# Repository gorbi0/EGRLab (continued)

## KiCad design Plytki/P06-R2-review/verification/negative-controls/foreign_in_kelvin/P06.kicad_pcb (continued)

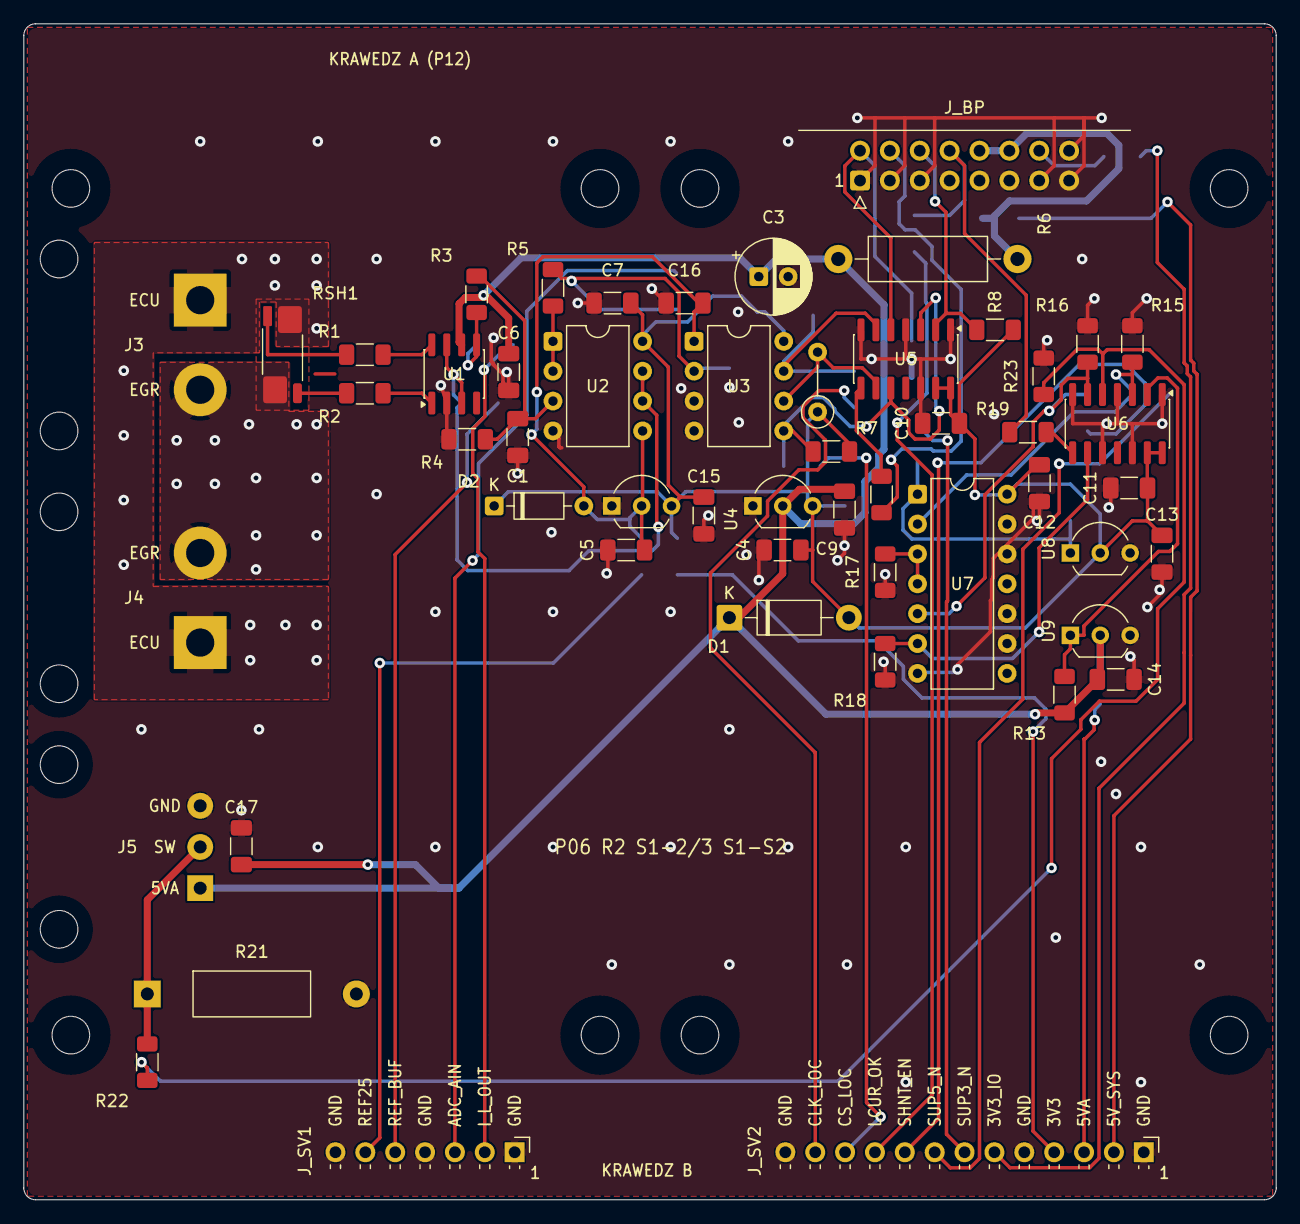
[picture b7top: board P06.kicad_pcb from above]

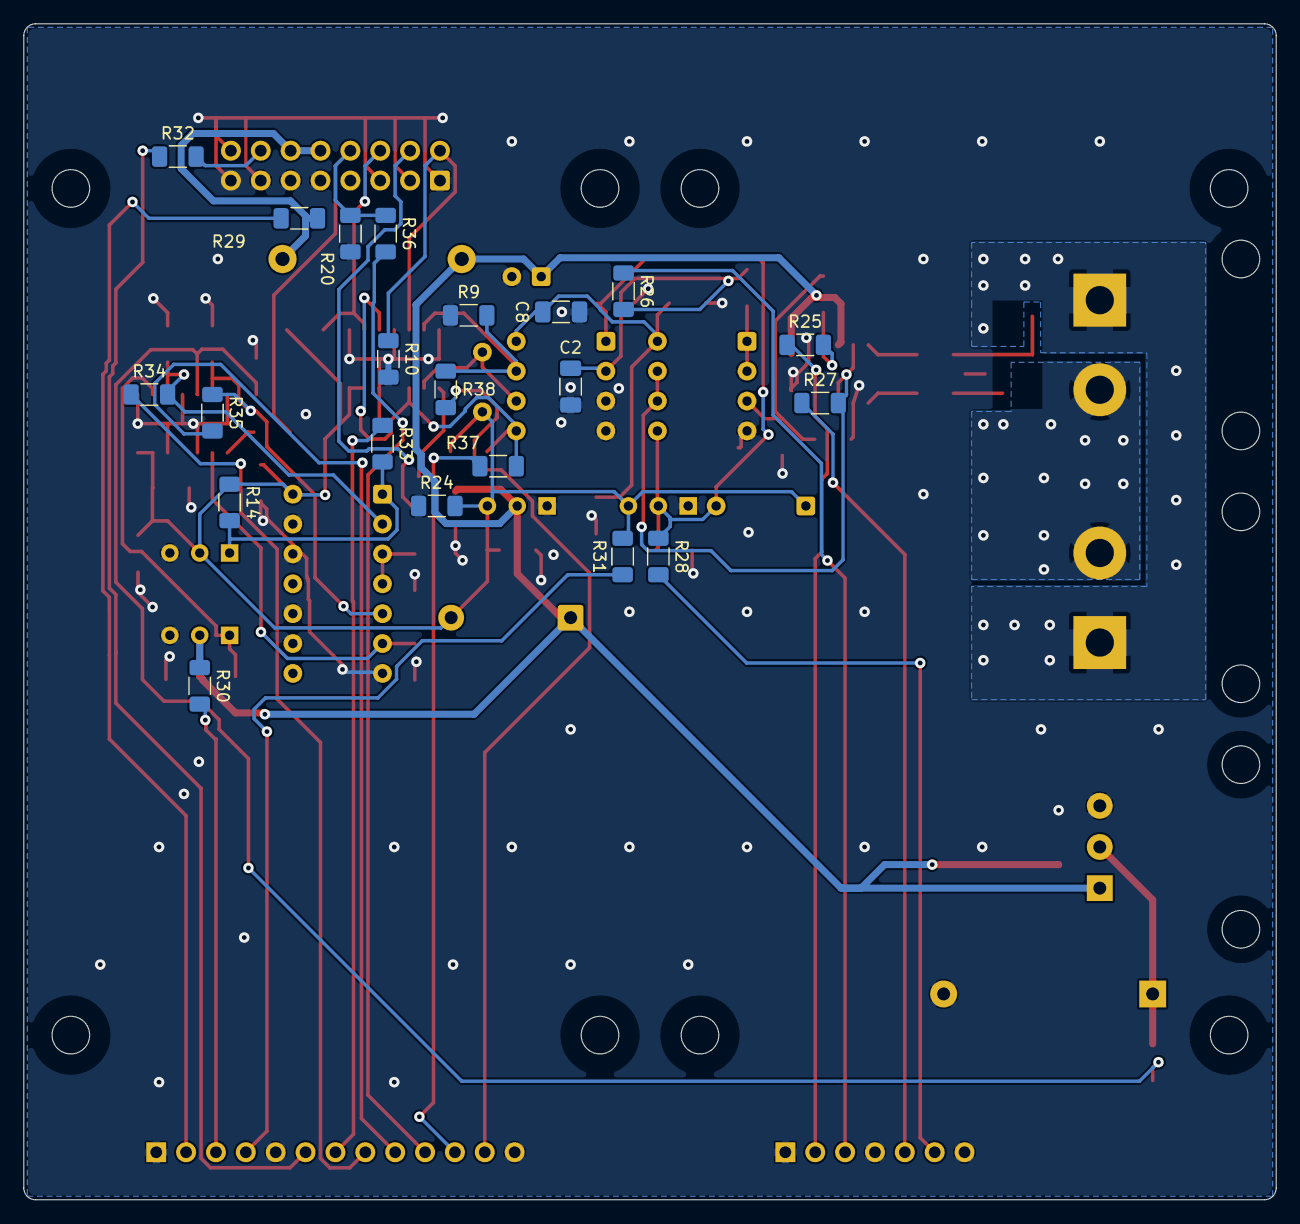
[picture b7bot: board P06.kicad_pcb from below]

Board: 2 copper layers, 106.5 x 100.0 mm, 82 parts (21 on the bottom side), 48 nets.

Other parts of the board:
C1: 470n; C_1206_3216Metric_Pad1.33x1.80mm_HandSolder
C5: 4.7u; C_1206_3216Metric_Pad1.33x1.80mm_HandSolder
C6: 100n; C_1206_3216Metric_Pad1.33x1.80mm_HandSolder
D2: BAT85; D_DO-35_SOD27_P7.62mm_Horizontal
H1, H2, H3, H4, H5, H6, H7, H8: M3 NPTH
R1, R2: 10R; R_1206_3216Metric_Pad1.30x1.75mm_HandSolder
R3, R4: 5.11K; R_1206_3216Metric_Pad1.30x1.75mm_HandSolder
U1: INA240A2; SOIC-8_3.9x4.9mm_P1.27mm
U10: MCP1525-I/TO; TO-92_Inline_Wide

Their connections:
3V3_P06: D2.1, U10.3; also elsewhere on the board
5VA_P06: C6.1, U1.6; also elsewhere on the board
/ANA/INA_MINUS: R2.2, U1.1
/ANA/INA_PLUS: R1.2, U1.8
/ANA/I_DIV: C1.1, R3.2, R4.1; also elsewhere on the board
GND: C1.2, C5.2, C6.2, R4.2, U1.2, U10.1; also elsewhere on the board
I_L_OUT: R3.1, U1.5; also elsewhere on the board
K_MINUS: R2.1; also elsewhere on the board
K_PLUS: R1.1; also elsewhere on the board
REF25: C5.1, D2.2, U10.2; also elsewhere on the board
REF_BUF: U1.3, U1.7; also elsewhere on the board

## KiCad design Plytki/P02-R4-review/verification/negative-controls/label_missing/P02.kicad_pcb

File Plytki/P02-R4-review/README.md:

# P02 R4 — zasilanie z pakietu Li-ion 4S (etap 2: PCB w formacie S1, klasa L)

**Nadruk 2.10.2026 (gałąź `p02-r4-nadruk`, przed zamówieniem):** wszystkie napisy ≥ 1,0 mm, linia ≥ 0,15 mm (minimum JLCPCB; ustalenie niezależnych recenzji P05 / P06), minimum w regułach DRC (`set_rules.py`). Miedź, otwory i rozmieszczenie bez zmian (wydanie odtworzone z zapisanego trasowania); paczka `P02-PCB-R4-zamowienie` zbudowana od nowa (DRC 0/0/0, CAM 20/20, próby CAM 8/8).

29.09.2026 schemat (sesja w chmurze, etap 1), 29–30.09.2026 PCB (lokalnie, etap 2). **Status: PCB i kontrole do recenzji. Pliki produkcyjne (Gerber, wiercenia), przymiarka 1:1 i zakupy nie są zrobione.** R4 zastępuje P01 PROTECT i część HOLD płytki P02 R3 zgodnie ze specyfikacją `Plytki/P02-R4-specyfikacja/` (D-01…D-07 przyjęte, R23 = 22 kΩ / 0,5 W). Zamknięte pakiety P01 R3 i P02 R3 nie zostały zmienione, generatory skopiowano stamtąd.

## Co jest na płytce

- **WEJ** (plik `P02.kicad_sch`): J1 z pakietu, Q9 (Q_REV) i Q1 (Q_SW) — dwa SUP53P06 połączone przeciwsobnie źródłami w SW_COM; tor bramki Q1 z szybkim wyłączaniem Q2 (Q_OFF) i Q3–Q5 przeniesiony 1:1 z P01 R3 (poza R23). Dalej VSW (5KP18A, 47 µF), VMOTOR przez F1 5 A MINI, D1 (suma VSW i C_H → VLOG), podtrzymanie R40 22 Ω bezpiecznikowy → D2 → C12 2200 µF.
- **STER**: AUX5 z LM2936 zasilanego z SW_COM lub VLOG (D11/D12), REF TL431, UVLO na U2B z przełącznikiem PWR (J14) w górnej gałęzi dzielnika, OK z resetem U4, ENABLE przez D7/D8/Q6, PFAIL_N z U2A, SAFE_N/PG do P04 (Q7/Q8, R34, J13) i LED PWR.
- **LV**: TSR 2-2450 i TSR 2-2433 za F2/F3 1 A MINI, J3–J10 bez zmian.
- **MON**: PSU_OK jak R3 (U7, U8, U9 na adapterze, U10A; bramki HOLD_READY usunięte), J12 z PFAIL_N na pinie 3, VBAT auta J15 → R38 10 kΩ → D13 P6KE24CA → J11 Mini-Fit 2p.

Oznaczenia: tor sterowania ma numery z P01 R3 (Q1–Q8, R1–R4, R13–R34, C1–C11, D3/D4/D7–D9, U1–U4), elementy z P02 R3 dostały nowe numery. Pole `source_ref` w `docs/parts.json` podaje pochodzenie każdej części (`P01R3:…`, `P02R3:…`, `R4:NEW`): 54 z P01 R3, 34 z P02 R3, 43 nowe (w tym 17 punktów pomiarowych).

## Wyniki (szczegóły: `verification/QA.md`, `docs/OBLICZENIA-R4.md`)

| Kontrola | Wynik |
|---|---|
| ERC (4 arkusze) | 0 naruszeń |
| Netlista pin po pinie względem `parts.py` | 131 części, 317/317 pinów, 61 sieci |
| Kontrole elektryczne | 35/35 PASS |
| Próby ujemne | 19/19 (18 mutacji wykrytych + próba zerowa czysta) |
| UVLO nominalnie / obwiednia | 13,50 / 12,55 V; załączenie 12,90–14,08 V, wyłączenie 11,98–13,11 V, histereza ≥ 0,84 V |
| Wyłączenie Q1 (R23 22 kΩ) | 44–71 µs nominalnie, do 239 µs w narożniku (model skalibrowany na ngspice P01 R3: −6…−9 %) |
| Narastanie VSW / prąd przy 220 µF | 11,5 V/ms / 2,53 A nominalnie (5,6–14,7 V/ms, do 3,24 A w narożnikach) |
| Podtrzymanie po PFAIL_N przy 6 W | 16,8 ms nominalnie, 11,1 ms w najgorszym narożniku |

Niezgodności ze specyfikacją (do decyzji, opisane w `docs/OBLICZENIA-R4.md`): Z-02 (rozrzut większy niż ± 0,34 V), Z-08 (najgorszy narożnik 11,1 / 22,3 ms zamiast 14 / 28 ms), Z-01 (25 V wbrew 5KP18A). Odstępstwo projektowe: PFAIL_N z U2A buforującej OK zamiast porównania UV_CMP (D-06 dosłownie).

## Uruchomienie

W chmurze: `scripts/egrlab-docker python3 src/run_schematic.py` (ok. 20 s). Lokalnie: Python KiCada 10.0.6, `KICAD_CLI` i `PDFTOPPM` wskazują narzędzia. Kroki: budowa schematu → ERC → netlista → `verify_schematic.py` → `check_electrical.py --negative` → PDF i podglądy PNG → `verification/manifest.json`.

PCB (lokalnie, ok. 25 min): Python KiCada 10.0.6 `src/run_release.py` — schemat, płytka odtworzona z `routing/P02.ses` i `routing/completion-routes.json`, nadruk, `verify_pcb.py`, próby ujemne, widoki, PDF, QA i manifest. Zmienne: `EGRLAB_PDF_PYTHON` (reportlab), `EGRLAB_NODE` i `EGRLAB_SHARP` (rasteryzacja), `PDFTOPPM`; `--new-route` uruchamia Freerouting od nowa (`EGRLAB_FREEROUTING`). Trasowania nie robić w chmurze (`docs/CHMURA.md`, zasada 6).

## Zawartość

| Ścieżka | Zawartość |
|---|---|
| `eda/` | Projekt KiCad 10 (4 arkusze A3), lokalne biblioteki symboli i footprintów |
| `output/pdf/P02-R4-schemat.pdf`, `output/previews/` | Schemat i podglądy stron |
| `docs/parts.json`, `docs/BOM.csv` | Części, piny, sieci, MPN, pochodzenie |
| `docs/OBLICZENIA-R4.md` | UVLO, PFAIL_N, wyłączanie z R23, narastanie VSW, podtrzymanie, straty |
| `verification/` | ERC, netlista, kontrola pin po pinie, kontrole elektryczne, próby ujemne, logi, manifest SHA-256 |
| `src/` | Generatory (`cadlib.py`, `verify_schematic.py` z P02 R3), `parts.py`, `build_schematic.py`, `check_electrical.py`, `run_schematic.py` |

Footprinty TO-220, MFR-50, PR02, B32529, MKS2, P600 i wiązki PG pochodzą z bibliotek P01 R3 / P02 R3 (bez zmian), pozostałe z KiCad 10.0.6 albo z generatora w `parts.py`. W etapie 2 (PCB) trzeba potwierdzić: obrys C12 (16 × 25 mm, P7,5), oprawki MINI Keystone 3568, Mini-Fit 2p.

## Etap 2 — PCB (format S1, klasa L; lokalnie 29–30.09.2026)

**Płytka:** 160 × 100 mm, klasa L — cały poziom 1 stosu (sloty S1–S3; format S1-3: w klasie 2/3 trasowanie się nie domykało, decyzja użytkownika „opcja 1”). Dwie warstwy 35 µm, FR4 1,6 mm. J_BP (IDC 2×10 kątowe) na krawędzi A w slocie S3, listwy serwisowe J_SV1 (S1) i J_SV2 (S3) na krawędzi B, złącza pakietu i silnika przy ścianie wejść (x = 160).

**Rozmieszczenie** (`src/placement.py`):
- blok mocy z pilota 2/3 przesunięty o 53,5 mm do ściany wejść (wylewki, pasy 5 A i korytarz tym samym przesunięciem w `route_critical.py`); rdzeń mocy (Q9, Q1, Q2, sterowanie bramki, F1, D3) bez zmian — decyzja użytkownika 30.09, jego miedź jest narysowana wokół położeń części;
- blok sterowania rozsunięty w osi x od strony panelu dwa razy: ×1,35, potem na wskazanie użytkownika (wolne pole między blokami na wydruku 1:1) górna połowa ×1,25, dolna ×1,12; układy jadą sztywno ze swoimi kondensatorami odsprzęgającymi i rezystorami serwisowymi;
- grupa podtrzymania (C12, D1, D2, R40, R41, R67, C20, R68) 8 mm w lewo razem ze swoimi wylewkami VLOG/HOLD_C i przedłużeniami VSW; grupa ENABLE (Q6, D7, D8, R14–R16, R55) 4 mm w lewo;
- R5 (1 kΩ, początek dzielnika UVLO) obok D11 (SW_COM): PWR_A (R5 → J14 → włącznik na panelu) krótka, rezystor nadal przy źródle;
- zajętość obrysami w pasach 20 mm po rozsunięciu: 42 / 43 / 41 / 40 / 41 / 23 / 76 / 68 % (wcześniej 49 / 60 / 36 / 24 / 29 / 34 / 76 / 68 %).

**Trasowanie:** Freerouting 2.1.0, 30 przejść; domknęła się 1. próba (`routing/P02.ses`, `routing/attempts.json`). Planer dokańczania dołożył 7 tras w 7 sieciach (`routing/completion-routes.json`). Płytkę odtwarza `src/run_layout.py --reuse-ses` (bez routera).

**Poprawki łańcucha względem pilota** (w kodzie opisane datami 29–30.09):
- planer dokańczania kończy ścieżkę tylko na warstwie pola (wcześniej ścieżka B.Cu kończyła się na polu SMD F.Cu bez przelotki);
- zszywanie GND na całej długości płytki (pilot kończył siatkę na x = 104,5) i wiązanie klastrów GND bez połączenia z J1.2; kontrola obecności obu stref GND;
- porządki: przelotki na polach THT tej samej sieci, przelotki z miedzią na jednej warstwie; łańcuch uznawany za nadmiarowy tylko wtedy, gdy oba końce leżą na tej samej grupie zablokowanej miedzi;
- wylewki BAT_IN i VSW pod końcami blaszek Q9 i Q1 (wcześniej wchodził tam pasek GND);
- nadruk: etykiety listew przed oznaczeniami, oznaczenia poza nadrukiem części, litery „K” diod przesuwane z linii nadruku;
- kontrole: obrys bez grubości linii, tor 5 A liczony jako miedź sieci na przekroju, niezgodności z biblioteką tylko dla części z przyciętym nadrukiem; próby ujemne i PDF we współrzędnych klasy L.

**Wyniki** (`verification/QA-PCB.md`, `verification/pcb-checks.json`):

| Kontrola | Wynik |
|---|---|
| DRC (świeży, wszystkie poziomy) | 0 niepołączonych, 0 niezgodności ze schematem, 0 innych naruszeń; 14 × `lib_footprint_mismatch` u części, którym `silkscreen.py` przyciął nadruk lub przesunął tekst (lista w `routing/silkscreen.json`) |
| Kontrole PCB | 23/23 |
| Próby ujemne | 12/12 (w tym próba zerowa) |
| Tor 5 A — najwęższy przekrój miedzi (wymóg 4,0 mm, IPC-2152, 35 µm, ΔT ≤ 20 K) | BAT_IN 6,0; SW_COM 6,1; VSW 5,1; VMOTOR 5,7; powrót GND na B.Cu 4,1 mm |
| Pola z pełnym połączeniem ze strefą | C8.2, D3.2, LED1.1, U10.4, U2.4 (odciążenie „zagłodzone” przez sąsiednie ścieżki); złącza zachowują odciążenia |
| Wysokości | ≤ 21,5 mm; C27/C28 od spodu 0,88 mm (karta KEMET C1206C104K5RACTU, DigiKey 411248) |

**Do recenzji / otwarte:**
- przymiarka 1:1 (wydruk z `output/pdf/P02-R4-PCB.pdf`);
- 9 oznaczeń ukrytych z braku miejsca (R23, R22, Q2, Q9, F3, F1, F2, U6, U5); nie wstawione znaczniki „1” przy złączach (piny 1 oznacza nadruk footprintów);
- pola z pełnym połączeniem ze strefą GND lutować mocniejszą lutownicą — szczególnie D3.2 (wyprowadzenie transila P600);
- najwęższy przekrój toru 5 A: 4,1 mm;
- awaria jednego przebiegu wydania 30.09 (strefy GND zniknęły po imporcie SES, 204 niepołączenia) nie dała się odtworzyć; `stitch.py` zatrzymuje się teraz, gdy stref GND brakuje.

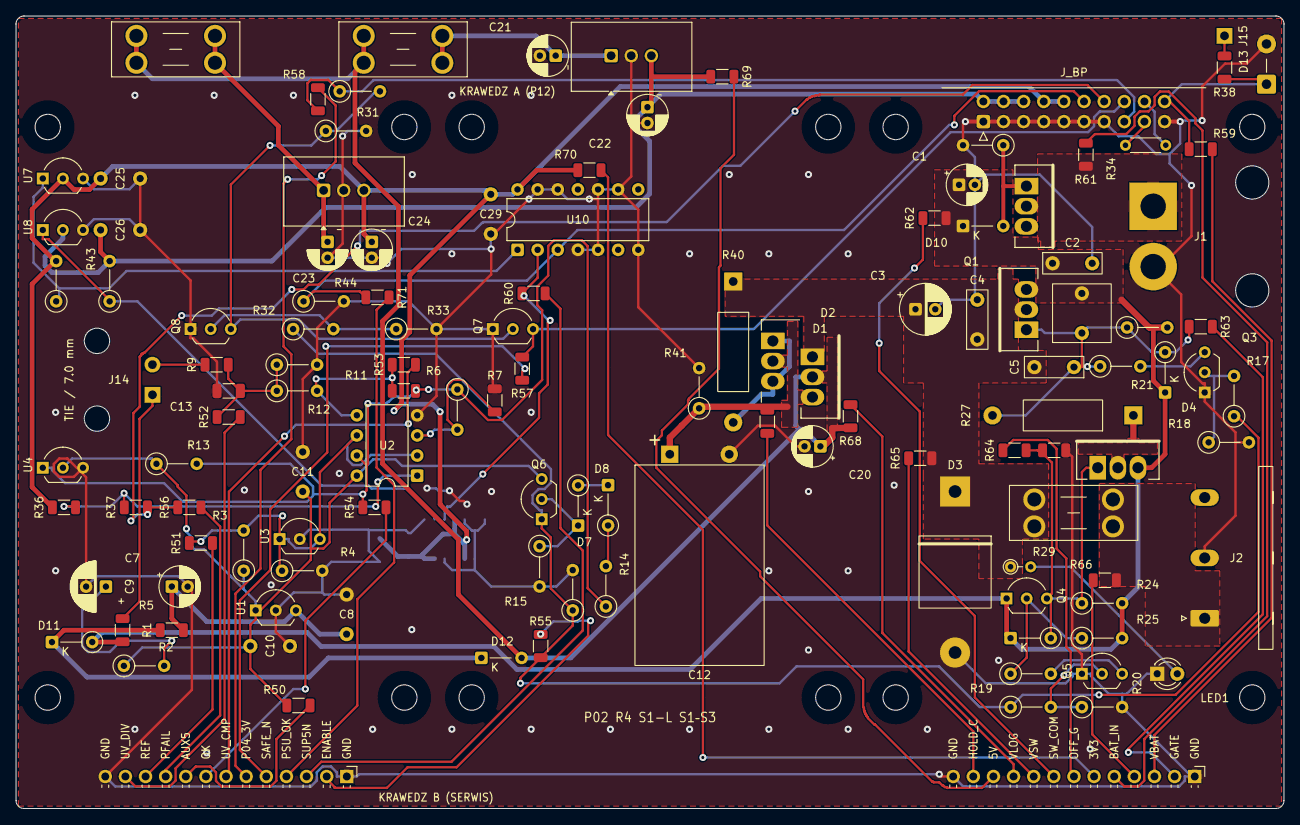
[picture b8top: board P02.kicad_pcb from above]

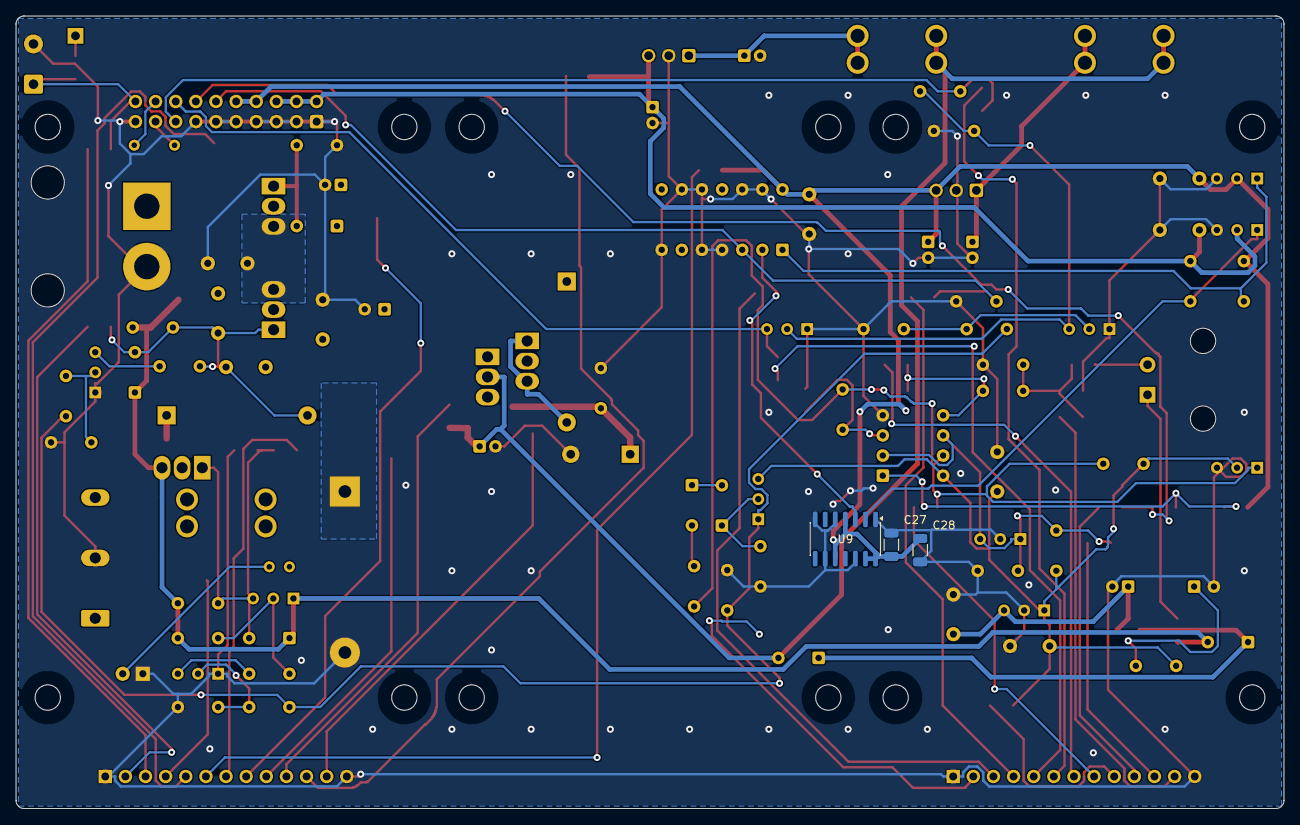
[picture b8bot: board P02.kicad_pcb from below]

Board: 2 copper layers, 160.0 x 100.0 mm, 139 parts (3 on the bottom side), 73 nets.

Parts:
C1, C21, C23: 10u; CP_Radial_D5.0mm_P2.00mm
C2, C4: 100nF; C_TDK_B32529_L7.3_W2.5_P5
C3, C9: 47u; CP_Radial_D6.3mm_P2.50mm
C5: 10nF; C_TDK_B32529_L7.3_W2.5_P5
C6: 1uF; C_WIMA_MKS2_1u100V_L7.2_W7.2_P5
C7, C20, C22, C24: 22u; CP_Radial_D5.0mm_P2.00mm
C8, C10, C11, C25, C26, C29: 100nF; C_Vishay_K15_H5_P5
C12: 2200u; CP_Radial_D16.0mm_L25mm_P7.50mm_Lying
C13: 10nF; C_1206_3216Metric
C27, C28: 100nF; C_1206_3216Metric
D1, D2: STPS20100CT; TO220_3_P2.54_Drill1.4
D3: 5KP24A; TVS_P600_P20.32
D4, D9, D10: BZX55C15; D_DO-35_SOD27_P5.08mm_Vertical_CathodeUp
D7, D8, D11, D12: 1N4148; D_DO-35_SOD27_P5.08mm_Vertical_CathodeUp
D13: P6KE24CA; D_DO-15_P5.08mm_Vertical_CathodeUp
F1: 5A; Fuseholder_Blade_Mini_Keystone_3568
F2, F3: 1A; Fuseholder_Blade_Mini_Keystone_3568
H1, H2, H3, H4, H5, H6, H7, H8, H9, H10, H11, H12: M3 NPTH
J1: BAT; Pigtail_PWR_2x2.5mm2
J2: VMOTOR; PhoenixContact_GMSTBA_2,5_3-G-7,62_1x03_P7.62mm_Horizontal
J14: PWR; Pigtail_PWR_SW_2xAWG22_T7
J15: VBAT_IN; Pigtail_VBAT_1xAWG22
J_BP: J_BP; IDC-Header_2x10_P2.54mm_Horizontal
J_SV1: J_SV1; PinHeader_1x13_P2.54mm_Horizontal
J_SV2: J_SV2; PinHeader_1x13_P2.54mm_Horizontal
LED1: GREEN 3mm; LED_D3.0mm
Q1, Q2, Q9: SUP53P06-20; TO220_3_P2.54_Drill1.4
Q3, Q5, Q6, Q7, Q8: 2N5551G; TO-92_Inline_Wide
Q4: 2N5401YBU; TO-92_Inline_Wide
R1: 47R; R_1206_3216Metric
R2: 1R; R_Axial_DIN0207_L6.3mm_D2.5mm_P5.08mm_Vertical
R3: 820R; R_Axial_DIN0207_L6.3mm_D2.5mm_P5.08mm_Vertical
R4, R10, R12, R16, R26, R30, R32, R41, R42, R43, R44: 10K; R_Axial_DIN0207_L6.3mm_D2.5mm_P5.08mm_Vertical
R5, R37, R50, R54, R55, R56, R57, R58, R60, R69, R70, R71: 1K; R_1206_3216Metric
R6, R15, R21, R24, R31, R35: 100K; R_Axial_DIN0207_L6.3mm_D2.5mm_P5.08mm_Vertical
R7: 150K; R_1206_3216Metric
R9: 41K2; R_1206_3216Metric
R11: 464K; R_1206_3216Metric
R13: 2K2; R_Axial_DIN0207_L6.3mm_D2.5mm_P5.08mm_Vertical
R14, R17, R19: 4K7; R_Axial_DIN0207_L6.3mm_D2.5mm_P5.08mm_Vertical
R18, R20, R25, R33: 47K; R_Axial_DIN0207_L6.3mm_D2.5mm_P5.08mm_Vertical
R22: 470K; R_Axial_DIN0207_L6.3mm_D2.5mm_P5.08mm_Vertical
R23: 22K; R_1206_3216Metric
R27: 10R; R_PR02_P17.78
R29: 6K8; R_Axial_DIN0204_L3.6mm_D1.6mm_P2.54mm_Vertical
R34: 0R; R_Axial_DIN0204_L3.6mm_D1.6mm_P5.08mm_Horizontal
R36, R38, R51, R52, R53, R59, R63, R64: 10K; R_1206_3216Metric
R40: 22R; R_PR02_P17.78
R61, R62, R65, R66, R67, R68: 4K7; R_1206_3216Metric
U1: LM2936Z-5.0; TO-92_Inline_Wide
U2: LM2903P; DIP-8_W7.62mm
U3: TL431BILP; TO-92_Inline_Wide
U4, U8: MCP120-450DI/TO; TO-92_Inline_Wide
U5: TSR 2-2450; Converter_DCDC_TRACO_TSR2-xxxx_THT
U6: TSR 2-2433; Converter_DCDC_TRACO_TSR2-xxxx_THT
U7: MCP120-300DI/TO; TO-92_Inline_Wide
U9: 74LVC125A; SOIC-14_3.9x8.7mm_P1.27mm
U10: SN74HC08N; DIP-14_W7.62mm

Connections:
3V3_IO: C24.1, C25.1, C27.1, C28.1, C29.1, J_BP.8, J_BP.10, R36.1, R42.2, R70.1, U6.3, U7.2, U9.4, U9.10, U9.13, U9.14, U10.14
5V_SYS: C22.1, C26.1, J_BP.2, J_BP.4, J_BP.6, R43.2, R69.1, U5.3, U8.2
/LV/P02_VIN_DC5: C21.1, F2.2, U5.1
/LV/P02_VIN_DC33: C23.1, F3.2, U6.1
/MON/P02_SUP3_N: R42.1, U7.1, U10.1
/MON/P02_SUP5_RAW: R43.1, U8.1, U9.2
/MON/VBAT_CAR: J15.1, R38.1
/P02_CH_A: D2.1, D2.3, R40.2
/P02_OFF_D: Q2.2, R27.1
/P02_ON_B: Q3.2, R17.2, R18.1
/P02_ON_COL: Q3.3, R21.2
/P02_REL_B: Q5.2, R19.2, R20.1
/P02_REL_COL: Q5.3, R26.2
/P02_REL_PB: Q4.2, R25.1, R26.1
/P02_REV_G: D10.2, Q9.1, R35.1
/SERW/P02_SV_3V3_IO: J_SV2.6, R70.2
/SERW/P02_SV_5V_SYS: J_SV2.11, R69.2
/SERW/P02_SV_AUX5: J_SV1.9, R50.2
/SERW/P02_SV_BAT_IN: J_SV2.5, R61.2
/SERW/P02_SV_ENABLE: J_SV1.2, R55.2
/SERW/P02_SV_GATE: J_SV2.2, R63.2
/SERW/P02_SV_HOLD_C: J_SV2.12, R67.2
/SERW/P02_SV_OFF_G: J_SV2.7, R64.2
/SERW/P02_SV_OK: J_SV1.8, R54.2
/SERW/P02_SV_P04_3V3: J_SV1.6, R58.2
/SERW/P02_SV_PFAIL_N: J_SV1.10, R56.2
/SERW/P02_SV_PSU_OK: J_SV1.4, R71.2
/SERW/P02_SV_REF: J_SV1.11, R51.2
/SERW/P02_SV_SAFE_N: J_SV1.5, R57.2
/SERW/P02_SV_SUP5_N: J_SV1.3, R60.2
/SERW/P02_SV_SW_COM: J_SV2.8, R62.2
/SERW/P02_SV_UV_CMP: J_SV1.7, R53.2
/SERW/P02_SV_UV_DIV: J_SV1.12, R52.2
/SERW/P02_SV_VBAT_SENSE: J_SV2.3, R59.2
/SERW/P02_SV_VLOG: J_SV2.10, R68.2
/SERW/P02_SV_VMOTOR: J_SV2.4, R66.2
/SERW/P02_SV_VSW: J_SV2.9, R65.2
/STER/P02_AUX_IN: C7.1, C8.1, R1.2, U1.3
/STER/P02_BUF_BASE: D8.1, Q6.2, R15.1
/STER/P02_BUF_D1: D7.2, R14.2
/STER/P02_BUF_D2: D7.1, D8.2
/STER/P02_C_AUX_TOP: C9.1, R2.2
/STER/P02_FAULT_B: Q7.2, Q8.3, R30.2, R31.1
/STER/P02_FAULT_REL_B: Q8.2, R32.2, R33.1
/STER/P02_LED_A: LED1.2, R29.2
/STER/P02_PFAIL_OC: R36.2, R37.1, U2.1
/STER/P02_PF_IN: R6.2, R7.1, U2.3
/STER/P02_PWR_A: J14.1, R5.2
/STER/P02_PWR_B: J14.2, R9.1
/STER/P02_V_CTRL: D11.1, D12.1, R1.1
GND: C1.2, C2.2, C3.2, C4.2, C7.2, C8.2, C9.2, C10.2, C11.2, C12.2, C13.2, C20.2, C21.2, C22.2, C23.2, C24.2, C25.2, C26.2, C27.2, C28.2, C29.2, D3.2, D13.2, J1.2, J2.2, J_BP.1, J_BP.3, J_BP.5, J_BP.7, J_BP.9, J_BP.11, J_BP.13, J_BP.19, J_SV1.1, J_SV1.13, J_SV2.1, J_SV2.13, LED1.1, Q3.1, Q5.1, Q7.1, Q8.1, R4.2, R7.2, R10.2, R15.2, R16.2, R18.2, R20.2, R23.2, R31.2, R33.2, R35.2, R41.2, R44.2, U1.2, U2.4, U3.2, U4.3, U5.2, U6.2, U7.3, U8.3, U9.1, U9.5, U9.7, U9.9, U9.12, U10.4, U10.5, U10.7, U10.9, U10.10, U10.12, U10.13
P02_AUX5: C10.1, C11.1, Q6.3, R2.1, R3.1, R13.1, R50.1, U1.1, U2.8, U4.2
P02_BAT_IN: J1.1, Q9.2, R61.1
P02_ENABLE: Q6.1, R16.1, R17.1, R19.1, R32.1, R55.1
P02_GATE: C5.1, C6.1, D4.2, Q1.1, R21.1, R22.1, R27.2, R63.1
P02_HOLD_C: C12.1, D1.3, D2.2, R41.1, R67.1
P02_OFF_G: D9.2, Q2.1, Q4.3, R23.1, R24.1, R64.1
P02_OK: R6.1, R11.1, R13.2, R14.1, R54.1, U2.7, U4.1
P02_REF: R3.2, R4.1, R51.1, U2.2, U2.6, U3.1, U3.3
P02_SUP5_N: R60.1, U9.3, U10.2
P02_SW_COM: C1.1, C2.1, C6.2, D4.1, D9.1, D10.1, D11.2, Q1.3, Q2.3, Q4.1, Q9.3, R5.1, R22.2, R24.2, R25.2, R62.1
P02_UV_CMP: R11.2, R12.2, R53.1, U2.5
P02_UV_DIV: C13.1, R9.2, R10.1, R12.1, R52.1
P02_VLOG: C20.1, D1.2, D12.2, F2.1, F3.1, R68.1
P02_VSW: C3.1, C4.1, C5.2, D1.1, D3.1, F1.1, Q1.2, R29.1, R40.1, R65.1
P04_3V3: J_BP.15, R30.1, R58.1
PFAIL_N: J_BP.14, R37.2, R56.1
PG_LINK: J_BP.18, R34.2
PG_SEND: J_BP.17, R34.1
PSU_OK: J_BP.12, R44.1, R71.1, U10.3
SAFE_N: J_BP.16, Q7.3, R57.1
VBAT_SENSE: D13.1, J_BP.20, R38.2, R59.1
VMOTOR: F1.2, J2.1, R66.1

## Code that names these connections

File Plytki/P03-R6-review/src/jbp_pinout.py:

"""P03 R6 (format S1): pinout of the three edge-A connectors J_BP1..J_BP3 (IDC 2x10, right angle, one per slot).
Single source for parts.py and docs/J_BP.csv. Ribbon order = pin number (1..20), so pin n neighbours n-1 and n+1.
Rules (task ZADANIE-P03-S1 §2): odd pins GND where possible; ADC_SCLK, SPI3_SCLK and MEAS_EN with GND on both sides;
an odd pin that is not GND carries only a static signal or a supply (exceptions listed in EXCEPTIONS with a reason).
Group moves against the task table (reasons in README): TEMP J_BP2 -> J_BP3 (P09 sits in S3), PFAIL_N J_BP3 -> J_BP2,
P07 group (DIR + ITEST) J_BP3 -> J_BP1. Without them J_BP2 or J_BP3 would carry 15 signals with 5 GND, which cannot give
every clock two GND neighbours and every edge signal one.
Columns: pin -> (net, direction seen from P03, target boards, note).
"""
G = ('GND', 'gnd', 'P12 (wszystkie)', '')
JBP = {
 'J_BP1': {  # slot S1: panel P11 (x = 0), P10 CAN, P06 ILOG, P08 SENSOR, P07 (DIR, ITEST)
  1: G, 2: ('CS_ILOG_N', 'out', 'P06', 'U22 (dekoder U2 Y0)'), 3: G, 4: ('CS_ITEST_N', 'out', 'P07', 'U22 (dekoder U2 Y1)'), 5: G,
  6: ('CAN_TX', 'out', 'P10', 'GPIO17 bezposrednio'), 7: G, 8: ('CAN_RX', 'in', 'P10', 'U11, domyslnie 1 (recessive)'), 9: G,
  10: ('N_J_SCOPE_HOT', 'out', 'P11 (BNC SCOPE)', 'SCOPE_TRIG przez R12 330R'),
  11: ('LOGGER_CURRENT_OK', 'in', 'P06', 'statyczny; wyjatek od GND na nieparzystym'), 12: ('SENSOR_HEALTHY', 'in', 'P08', 'statyczny'),
  13: ('MARK', 'in', 'P11', 'przycisk; statyczny; wyjatek'), 14: ('TEST_KEY', 'in', 'P11', 'przelacznik; statyczny'),
  15: ('LOGGER_CLEAR', 'in', 'P11', 'przycisk; statyczny; wyjatek'), 16: ('TEST_PRESENT', 'in', 'P11', 'statyczny'),
  17: ('ENA_DIAG', 'in', 'P07', 'statyczny; wyjatek'), 18: ('ENB_DIAG', 'in', 'P07', 'statyczny'),
  19: ('MOTOR_INA', 'out', 'P07', 'MCP23017, statyczny; wyjatek'), 20: ('MOTOR_INB', 'out', 'P07', 'MCP23017, statyczny')},
 'J_BP2': {  # slot S2: P05 DAQ (poziom 3, S1-S2), wspolna magistrala ADC do P05/P06/P07, PFAIL_N i 5V_SYS z P02 R4
  1: G, 2: ('ADC_SCLK', 'out', 'P05, P06, P07', 'zegar; GND po obu stronach; P12 rozprowadza wielopunktowo'), 3: G,
  4: ('ADC_DOUTA', 'in', 'P05, P06, P07', 'wspolna linia danych; P12 wielopunktowo'), 5: G, 6: ('ADC_SDI', 'out', 'P05', ''), 7: G,
  8: ('ADC_CS', 'out', 'P05', ''), 9: G, 10: ('ADC_CONVST', 'out', 'P05', 'zbocze startu przetwarzania'), 11: G,
  12: ('ADC_BUSY', 'in', 'P05', ''), 13: G, 14: ('MEAS_EN', 'out', 'P05', 'GND po obu stronach'), 15: G,
  16: ('ADC_RESET', 'out', 'P05', 'statyczny'), 17: G, 18: ('PFAIL_N', 'in', 'P02 R4', 'aktywny niski; na P03 1k szeregowo + 10k do 3V3_CORE'),
  19: ('5V_SYS', 'pwr', 'P02 R4', 'zasilanie P03; wyjatek od GND na nieparzystym'), 20: ('5V_SYS', 'pwr', 'P02 R4', 'zasilanie P03')},
 'J_BP3': {  # slot S3: P04 SAFE (poziom 4, S2-S3), P09 TEMP (poziom 3, S3), 3V3_IO z P02 R4
  1: G, 2: ('SPI3_SCLK', 'out', 'P09', 'zegar; GND po obu stronach'), 3: G, 4: ('SPI3_MOSI', 'out', 'P09', ''),
  5: ('3V3_IO', 'pwr', 'P02 R4', 'zasilanie OE U14; wyjatek (zasilanie odsprzezone)'), 6: ('SPI3_MISO', 'in', 'P09', 'wspolne z karta SD na P03'), 7: G,
  8: ('TC1_CS', 'out', 'P09', ''), 9: ('SENSOR_ENABLE', 'out', 'P04', 'MCP23017, statyczny; wyjatek'), 10: ('TC2_CS', 'out', 'P09', ''), 11: G,
  12: ('SUP_N_OUT', 'out', 'P04', 'reset przez U6 (Schmitt) i R41 220R'), 13: ('CORE_LINK', 'out', 'P04', '3V3_CORE przez R14 1k, statyczny; wyjatek'),
  14: ('PWM', 'out', 'P04', 'GPIO1 bezposrednio'), 15: G, 16: ('HEARTBEAT', 'out', 'P04', 'GPIO21 bezposrednio'),
  17: ('HW_ARMED', 'in', 'P04', 'statyczny; wyjatek'), 18: ('MCU_ARM', 'out', 'P04', 'statyczny'), 19: G,
  20: ('INTERLOCK', 'in', 'P04', 'statyczny')},
}
EXCEPTIONS = {  # odd pins that are not GND, with the one-line reason required by the task
 ('J_BP1', 11): 'J_BP1 ma 15 sygnalow (panel, CAN, ILOG, SENSOR, P07); piny 11-19 to blok sygnalow statycznych',
 ('J_BP1', 13): 'jw.', ('J_BP1', 15): 'jw.', ('J_BP1', 17): 'jw.', ('J_BP1', 19): 'jw.',
 ('J_BP2', 19): 'druga zyla 5V_SYS (IDC ok. 1 A na styk); zasilanie, nie sygnal',
 ('J_BP3', 5): '3V3_IO (zasilanie odsprzezone) jako powrot AC dla SPI3_MOSI/MISO',
 ('J_BP3', 9): 'SENSOR_ENABLE statyczny miedzy liniami CS termopar',
 ('J_BP3', 13): 'CORE_LINK statyczny (1k z 3V3_CORE)',
 ('J_BP3', 17): 'HW_ARMED statyczny (wejscie odpytywane przez U12)',
}

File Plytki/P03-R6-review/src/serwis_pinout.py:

"""P03 R6 (format S1 §6): three right-angle 1x13 service headers on edge B, one per slot, GND on pins 1 and 13.
Every other pin reaches its node through a series resistor placed at the node: 1K for rails <= 5 V and driven logic,
10K for high-impedance nodes (pull-up/pull-down or open-drain only). Content from docs/ODBIOR.md (R5).
30.09 (layout): pins grouped by the position of their nodes on the board (J_SV1 = nodes in S1, J_SV2 = S2, J_SV3 = S3), so the
lines from the resistors to the headers stay in their slot; the first router runs left 12 of 33 service lines crossing the board.
1.10 (review, user decision): inside each header the rails sit next to each other and next to 10K lines already pulled up, so a
slipped probe cannot drive a logic input from a rail through 2 kOhm; order kept close to the routable one of 30.09 (the variants with
the rails on pins 2-3 and the one with the fewest straight-line crossings did not complete routing); SUP_N_OUT through 10K (exception).
Pin -> (node net, resistor value, purpose). The header-side net is named SV_<node>.
"""
SERWIS = {
 'J_SV1': {  # S1: MCP23017, dekoder, panel (LOGGER_CURRENT_OK od 30.09: bufor U14), I2C
  # 1.10 (recenzja, decyzja użytkownika): kolejność z 30.09 (ta się trasowała) z minimalnymi zmianami: szyny 3V3_IO / 3V3_CORE obok siebie
  # (9-10), z drugiej strony linie I2C (10K, i tak podciągnięte do 3,3 V); LOGGER_CURRENT_OK przy GND i SDA (poślizg sondy daje "nie OK");
  # MOTOR_INB/INA przy GND i MEAS_BANK (start 0), z dala od szyn i linii trzymanych w stanie wysokim (pływające wejścia MCP przy starcie)
  2: ('MOTOR_INB', '1K', 'MCP23017; brak ruchu przy starcie'), 3: ('MOTOR_INA', '1K', 'MCP23017; brak ruchu przy starcie'),
  4: ('MEAS_BANK', '1K', 'wejscie A dekodera, start: 0'), 5: ('CS_ILOG_N', '1K', 'start: 1'), 6: ('SCOPE_TRIG', '1K', 'wyjscie GPIO41 przed R12'),
  7: ('CS_ITEST_N', '1K', 'start: 1'), 8: ('I2C_SCL', '10K', 'I2C MCP23017 (OD, 4k7)'), 9: ('3V3_IO', '1K', 'szyna z P02 R4 (OE U14)'),
  10: ('3V3_CORE', '1K', 'LDO modulu; zapad przez 3,07 V'), 11: ('I2C_SDA', '10K', 'I2C MCP23017 (OD, 4k7)'),
  12: ('LOGGER_CURRENT_OK', '1K', 'z P06 (10k R2 do GND)')},
 'J_SV2': {  # S2: zasilanie 5 V, nadzor, PFAIL_N, DAQ, SD
  # 1.10: kolejność z 30.09 z jedną zamianą (PFAIL_N <-> CURRENT_CS_N): szyny 5 V na końcach przy GND, obok PFAIL_N i SUP_RAW_N (10K)
  2: ('5V_SYS', '1K', 'szyna z P02 R4; tabela zasilania P02/USB'), 3: ('PFAIL_N', '10K', 'wejscie z P02 R4 po stronie zlacza (100k R43)'),
  4: ('ADC_RESET', '1K', 'start bez firmware: 0'), 5: ('MEAS_EN', '1K', 'start bez firmware: 0'), 6: ('ADC_BUSY', '1K', 'odpowiedz P05 na CONVST'),
  7: ('ADC_CONVST', '1K', 'start bez firmware: 0'), 8: ('ADC_CS', '1K', 'start: 1 (nieaktywne)'),
  9: ('CURRENT_CS_N', '1K', '/G dekodera U2, start: 1'), 10: ('SD_CS', '1K', 'karta SD, start: 1'),
  11: ('SUP_RAW_N', '10K', 'wyjscie TPS3808 (OD, 10k R13)'), 12: ('5V_M1', '1K', 'zasilanie modulu za blokada U5/Q1; USB-only, prad wsteczny')},
 'J_SV3': {  # S3: SAFE P04, TEMP P09, reset do P04; SUP_N od 30.09 (wezel przy U6)
  2: ('MCU_ARM', '1K', 'GPIO39; bez ARM stale 0'), 3: ('HEARTBEAT', '1K', 'GPIO21 do P04'), 4: ('PWM', '1K', 'GPIO1 do P04'),
  5: ('CORE_LINK', '10K', 'R14 1k z 3V3_CORE; na P04 >= 2,7 V'),
  6: ('SUP_N_OUT', '10K', 'reset do P04 za U6/R41; 10K (1.10, wyjatek od S1 par. 6): galaz serwisowa nie spowalnia zbocza resetu'),
  7: ('SENSOR_ENABLE', '1K', 'MCP23017 GPA3 do P04'), 8: ('TC2_CS', '1K', 'start: 1'), 9: ('TC1_CS', '1K', 'start: 1'),
  10: ('INTERLOCK', '1K', 'z P04'), 11: ('HW_ARMED', '1K', 'z P04; stale L w probach resetu'),
  12: ('SUP_N', '10K', 'wspolny reset = EN modulu (J1-3) + RESET MCP23017')},
}

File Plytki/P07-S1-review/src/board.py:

"""P07 S1 board configuration for the layout chain (format S1, class 2/3, slots S2-S3 of level 5). The generic layout scripts
(build_board, fanout_gnd, prepare_routing, run_layout, import_routing, stitch, complete_routes, cleanup, trim_stubs, silkscreen,
gndpath, ...) are copies of P06 R2 / P04 R3 src (P03 R6 chain via P09 R2 / P10 R2 / P05 R3; 5.10.2026, Ubuntu 24/7 session) and read
their board specific values from here. Geometry of the power block: placement.py and route_critical.py (docstrings).
"""
NAME = 'P07'                 # eda/P07.kicad_pcb, routing/P07.dsn / P07.ses, verification/P07.xml
REV = 'P07 S1'
TITLE = 'EGRLab P07 S1 DRIVE (IBT-2) / format S1, klasa 2/3, sloty S2-S3 poziomu 5'
DATE = '2026-10-05'
CLASS = '2/3'                # Plytki/Format-S1/format-s1.json 'klasy'
SLOTS = ['S2', 'S3']         # S1 section 7: P07 on level 5, slots S2-S3 (P08 in S1)
JBP = ['J_BP1', 'J_BP2']     # edge-A IDC (odd pins GND): GND comb in fanout_gnd.py
JSV = ['J_SV2']              # edge-B service header (one strip in slot S3, simplification 1 of 6.10)
GND_REF = ('J_BP1', '1')     # reference pad of the main GND cluster (stitch.py)
# Supply nets in class PWR: 5V_SYS (~110 mA with the KPWR coil, decision 5.10), the local rails and the logic supply. 0.4 mm with the
# S1 clearance 0.25 passes between DIP / SOIC-to-DIP pads (P04 R3).
PWR = ['5V_SYS', '5V_MOD', '5VA_P07', '3V3A_P07', '3V3_IO']
PWR_W, PWR_CLR = .4, .25
CORE = []
SIG_VIA = (.6, .3)           # 7.10 (sporne): signal / GND fan-out vias 0.6 / 0.3 (ring 0.15; JLCPCB 4-layer standard), were 0.9 / 0.4 of the 2-layer
                             # boards; power stitching (route_critical / stitch) and the PWR class keep 0.9 / 0.4
SIGNAL_W = .2                # Default track. 7.10 (sporne): 0.2 mm instead of 0.3 of P02-R3 (S1 has no number; JLCPCB 4 layers 0.09): the channel
                             # left of the relay did not take the logic links at 0.3 in 14 layout runs; clearance stays 0.25, PWR 0.4
# 10 A path (README: J1 -> K1 -> J2 / B+, J3 / M+ -> RSH1 -> J4) and the PGND return: locked pours on both layers (route_critical.py),
# out of the router's net list (prepare_routing.py), their pours exported as keepouts
FORCE = ['VMOTOR', 'PGND', 'MOD_BP', 'MOD_MP', 'T_EGR_P1', 'T_EGR_P3']
KELVIN = ['K_PLUS', 'K_MINUS', 'INA_PLUS', 'INA_MINUS']
# 7.10 (user decision): logic may cross the power block on In2.Cu (over the In1 PGND area); these analog nets (sheet ANA) may not
ANALOG_NETS = ['ADC_BUF', 'I_DIV', 'I_FILT', 'I_T_OUT', 'OC_FB', 'OC_HIGH', 'OC_LOW', 'REF25', 'REF_BUF', 'ADC_AIN', '3V3A_P07', '5VA_P07'] + KELVIN   # locked pair RSH1 -> R6 / R7 -> U1 (route_critical.py)
TAILS = ['J1', 'J2', 'J3', 'J4']                          # soldered 2.0 mm2 wires: J1 / J2 / J4 at x = 106.5, J3 at edge B (decisions 6.10 evening / 7.10)
SUPPORT_KEEPOUT = {r: 3.0 for r in TAILS}                 # NPTH cable-tie anchors: no copper within 3 mm of their centres
PIN_MARKS = {'J1': {'1': 'VM', '2': 'PG'}, 'J2': {'1': 'B+', '2': 'B-'}, 'J3': {'1': 'M+', '2': 'M-'}, 'J4': {'1': 'P1', '2': 'P3'}}   # S1 section 9
FINE = []                    # no fine-pitch parts
FINE_CLEARANCE, FINE_TRACK = .25, .3
GND_INNER = []
TOP_ONLY = []
ISOLATE = {}
SHUNT = 'RSH1'
# Router keepouts (pin-free): the strip between the Kelvin lines and around them up to the U1 pins (route_critical.py writes the exact
# box to routing/kelvin-box.json; placement.py fixes RSH1 / R6 / R7 / U1, so the values are constant here). Filled in below.
import json as _json, pathlib as _pl
_kb = _pl.Path(__file__).resolve().parents[1] / 'routing/kelvin-box.json'
_K = _json.loads(_kb.read_text()) if _kb.exists() else None
ROUTER_KEEPOUT = ([('F.Cu', *_K['f_box']), ('B.Cu', *_K['b_box'])] + ([('F.Cu', *_K['shunt_box'])] if 'shunt_box' in _K else [])) if _K else []
ANALOG_KEEPOUT = []
PLANNER_KEEPOUT = list(ROUTER_KEEPOUT)
# Decoupling (cap: (IC, supply pin, GND pin)): GND via at every 100 nF (stitch.py stage 4) and the return-path check (gndpath.py)
DEC_CAPS = {'C22': ('U1', '6', '2'), 'C23': ('U3', '8', '4'), 'C24': ('U4', '8', '4'), 'C25': ('U5', '8', '4'), 'C26': ('U6', '8', '4'),
            'C27': ('U7', '14', '7'), 'C28': ('U8', '2', '3'), 'C29': ('U9', '2', '3'), 'C30': ('U10', '14', '7'), 'C31': ('U11', '14', '7'),
            'C32': ('U12', '14', '7'), 'C33': ('U13', '14', '7'), 'C34': ('U14', '14', '7'), 'C35': ('U15', '14', '7'), 'C36': ('U16', '14', '7'),
            'C37': ('U2', '3', '1')}
EXTRA_GND_VIAS = [('pad', c, '2', 2.0) for c in DEC_CAPS]
FANOUT_REFS = []
FANOUT_MODE = 'all'   # 7.10: every top GND pad gets a via to the In1 GND plane before the router (GND islands were half of the open items left)
FANOUT_SKIP = []   # 7.10: U11 had GND on pins 7 and 13 (a bar across the body walled off SAFE_BAD U11.6 -> U11.9); pin 13 (unused 6A) now on 3V3_IO
# 7.10: locked links under a SOIC body before the router (fanout_gnd.py), (net, points); a point is a pad number (str) or footprint-local (x, y) mm.
# U16 has DRIVE_EN on 9 / 12 and DRV_OFF on 1 / 4 / 10 / 13: the router joined them round the outside of the pin rows and closed LEN_D (pin 11) in.
PRE_TIES = {'U16': [('DRIVE_EN', ['12', (.9, -1.27), (.9, 2.54), '9']),
                    ('DRV_OFF', ['13', (-.9, -2.54), (-.9, -3.81), '1']), ('DRV_OFF', [(-.9, -2.54), (-.9, 0.0), '4'])]}
SOIC_TIES = {}
RETURN_PAIRS = {c: (u, g) for c, (u, v, g) in DEC_CAPS.items()}
RETURN_ACCEPT = {}
# 7.10: force path exceptions ((net, layer): reason); checked on F.Cu, which carries the path to the shunt
FORCE_PATH_ACCEPT = {('MOD_MP', 'B.Cu'): 'J3.1 sits 6 mm under the shunt: on B.Cu its thermal gap and the rule area under RSH1 (F.Cu SMD) take the whole '
                                          '2.3 mm between them; the 4.5 mm PTH pad and its spokes carry the current to F.Cu, where the 4 mm corridor reaches the force pad'}
# 7.10: decoupling exceptions (cap: (accepted mm, reason)); moving them now means a new router draw
DEC_ACCEPT = {'C35': (7.0, 'U15 HC74 (ARM / latch, slow edges): 6.5 mm from pin 14, GND via at the pad (fan-out), In1 plane under both'),
              'C21': (12.0, 'second 100 nF on 3V3_IO at J_BP2 (C20 is the one at the pin); 11.4 mm, In1 plane under both')}
# In2.Cu supply regions (user decision 6.10: In2 = supplies + signals; 6.10 evening layout): DSN planes for the router (prepare_routing.py,
# as the GND plane of P03 R6: the router joins each supply pin to its plane with a via and routes other nets across it) and the real
# zones filled round the In2 signal tracks after the import (inner_zones.py). Each net: disjoint rectangles (x0, y0, x1, y1).
IN2_SUPPLY = {'3V3A_P07': [(0.6, 14.8, 30.0, 56.0)],                                     # 7.10 placement: ADC chain top left
              '5VA_P07': [(0.6, 56.5, 49.5, 92.0), (49.5, 68.0, 63.0, 82.0)],             # OC window / supervisors bottom left, INA240
              '3V3_IO': [(30.5, 14.8, 71.5, 31.0), (49.5, 54.5, 76.0, 67.5)]}             # logic under J_BP2 / under the relay

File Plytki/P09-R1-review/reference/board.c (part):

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#include "freertos/FreeRTOS.h"
#include "freertos/semphr.h"

enum { PWM = 1, ADC_SDI = 2, SCOPE = 41, ARM = 39, HW_ARM = 40, CURRENT_CS = 38,
       INTERLOCK = 42, HEART = 21, CONVST = 13, BUSY = 14 };

/* MCP23017 port A (wyjscia) */
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    ledc_set_duty(LEDC_LOW_SPEED_MODE, LEDC_CHANNEL_0, 0);
    ledc_update_duty(LEDC_LOW_SPEED_MODE, LEDC_CHANNEL_0);
}
bool board_interlock(void) { return gpio_get_level(INTERLOCK); }
bool board_armed(void) { return gpio_get_level(HW_ARM); }
bool board_mark(void) { return mark_pressed; }
bool board_local_current_present(bool test) {
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/* Wejscie w tryb rejestrow zalezy od zworek OS[2:0] = 111. Sprawdzamy to
 * zapisem i odczytem; wynik jest jawny, nie zgadywany. */
static void adc_probe_software_mode(void) {
    gpio_set_level(ADC_SDI, 0);
#if CONFIG_EGR_ADC_SOFTWARE_MODE
    software_mode = true;
    esp_err_t e = adc_reg_write_verified(ADC_REG_CONFIG, ADC_CONFIG_VALUE);
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                         .mode = GPIO_MODE_OUTPUT};
    ESP_ERROR_CHECK(gpio_config(&out));
    gpio_set_level(ARM, 0); gpio_set_level(HEART, 0); gpio_set_level(CONVST, 0);
    gpio_set_level(SCOPE, 0); gpio_set_level(ADC_SDI, 0);
    gpio_config_t inp = {.pin_bit_mask = (1ULL << HW_ARM) | (1ULL << INTERLOCK) | (1ULL << BUSY),
                         .mode = GPIO_MODE_INPUT};
    ESP_ERROR_CHECK(gpio_config(&inp));
    /* MARK moved to MCP GPB6. GPIO41 is now the scope output. */
    ledc_timer_config_t lt = {.speed_mode = LEDC_LOW_SPEED_MODE, .duty_resolution = LEDC_TIMER_10_BIT,
        .timer_num = LEDC_TIMER_0, .freq_hz = 1000, .clk_cfg = LEDC_AUTO_CLK};
    ESP_ERROR_CHECK(ledc_timer_config(&lt));
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    mcp_ready = true;
    ESP_ERROR_CHECK(porta_set(A_ADC_RESET, true)); esp_rom_delay_us(20);
    ESP_ERROR_CHECK(porta_set(A_ADC_RESET, false)); vTaskDelay(pdMS_TO_TICKS(10));
    spi_bus_config_t ab = {.mosi_io_num = ADC_SDI, .miso_io_num = 11, .sclk_io_num = 9,
        .quadwp_io_num = -1, .quadhd_io_num = -1, .max_transfer_sz = 32};
    ESP_ERROR_CHECK(spi_bus_initialize(SPI2_HOST, &ab, SPI_DMA_CH_AUTO));
    spi_device_interface_config_t ad = {.clock_speed_hz = CONFIG_EGR_ADC_SPI_HZ, .mode = 2, .spics_io_num = 12,
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    if (e != ESP_OK) { *sensor_fault = true; *log_present = true; *test_present = false; return e; }
    *sensor_fault = !(b & B_SENSOR_HEALTHY);
    *log_present = !(b & B_LOG_PRESENT_N);   /* HIGH = empty NC diagnostic chain; external 10k pull-down */
    *test_present = (b & B_TEST_PRESENT) != 0;
    return ESP_OK;
}
esp_err_t board_temperature(int ch, float *value, uint8_t *fault) {
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
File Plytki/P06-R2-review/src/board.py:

"""P06 R2 board configuration for the layout chain. The generic layout scripts (build_board, fanout_gnd, prepare_routing, run_layout,
import_routing, stitch, complete_routes, cleanup, trim_stubs, silkscreen, ...) come from P05 R3 (P03 R6 -> P09 R2 / P10 R2 -> P05 R3,
1.10.2026, Ubuntu 24/7 session) and read their board specific values from here.
"""
NAME = 'P06'                 # eda/P06.kicad_pcb, routing/P06.dsn / P06.ses, verification/P06.xml
REV = 'P06 R2'
TITLE = 'EGRLab P06 R2 I-LOGGER / format S1, klasa 2/3, sloty S1-S2 poziomu 4'
CLASS = '2/3'                # Plytki/Format-S1/format-s1.json 'klasy'
SLOTS = ['S1', 'S2']         # S1 section 7: P06 on level 4, slots S1-S2 (P10 in S3)
JBP = ['J_BP']               # edge-A IDC (odd pins GND): GND comb in fanout_gnd.py
JSV = ['J_SV1', 'J_SV2']     # edge-B service headers
GND_REF = ('J_BP', '1')      # reference pad of the main GND cluster (stitch.py)
PWR = ['5V_SYS', '5VA_P06', 'SW_RAW']   # class PWR (0.6 mm, clearance 0.3): J_BP -> R6 1 Ohm -> 5VA_P06 (180 mA in MEASURE, of it
                             # about 130 mA through the BYPASS status contact: J5.1 -> SW1 pole B -> J5.2 = SW_RAW -> R21 39 Ohm -> GND)
CORE = ['3V3_P06']           # class CORE3V3 (0.3 mm): LDO U4 output
SIGNAL_W = .3                # Default track: S1 section 3 (rules as P02-R3)
FORCE = ['ECU_P1', 'EGR_P1']  # motor current 5-6 A (10 A passive test E15): locked pours on both layers (route_critical.py), router keepouts
KELVIN = ['K_PLUS', 'K_MINUS', 'INA_PLUS', 'INA_MINUS']   # locked pair RSH1 -> R1 / R2 -> U1 (route_critical.py), out of the router's list
SUPPORT_KEEPOUT = {'J3': 3.0, 'J4': 3.0, 'J5': 3.0}   # NPTH cable-tie anchors of the three tails: no copper within 3 mm of their centres
PIN_MARKS = {'J3': {'1': 'ECU', '2': 'EGR'}, 'J4': {'1': 'ECU', '2': 'EGR'}, 'J5': {'1': '5VA', '2': 'SW', '3': 'GND'}}   # S1 section 9
FINE = []                    # no fine-pitch parts (SOIC 1.27 mm: S1 values reach every pin)
FINE_CLEARANCE, FINE_TRACK = .25, SIGNAL_W
GND_INNER = []               # (P05 R3: GND pins tied by an inner pour, out of the router's GND list)
# RSH1 at (22.0, 28.135) turned 270 (placement.py): courtyard x 20.08..23.93, y 23.73..32.54; Kelvin lines at y 28.135 / 31.415 into U1
# pins 8 / 1 at x 34.7. Keepouts hold only pins of the locked nets (force, Kelvin), which leave the router's net list (prepare_routing.py).
ROUTER_KEEPOUT = [('F.Cu', 19.8, 23.4, 24.2, 32.9),    # RSH1 courtyard (README: nothing foreign at the shunt)
                  ('F.Cu', 24.2, 27.3, 34.3, 32.4),    # between and around the Kelvin lines up to the U1 pins
                  ('B.Cu', 19.8, 27.3, 34.3, 32.4)]    # under the Kelvin lines: GND pour only, no router tracks
# review 2.10 (F2 / F3): the router ran service and supply tracks between the pin rows of U2 / U3 (SRV_ADC_AIN and SRV_I_L_OUT 22 mm
# under U2, SRV_CLK_LOCAL - the 500 kHz ADC clock behind 1k - and SRV_5VA_P06 under U3) and cut the B.Cu plane under both into a
# 191 mm2 island. Pin-free areas (0.1 mm off the DIP pads, U2 / U3 at x 45 / 52.62 and 57 / 64.62, pins y 27..34.62): both interiors
# on both layers, on B.Cu also the strip between them; C2 (bottom, under U3 at its IN+ / IN- pins, placement.py) keeps a pocket open
# towards them. No track and no via other than GND inside (verify_pcb.py); the GND pours fill them.
ANALOG_KEEPOUT = [('F.Cu', 45.9, 25.8, 51.72, 35.8), ('B.Cu', 45.9, 25.8, 51.72, 35.8),    # U2 interior
                  ('F.Cu', 57.9, 25.8, 63.72, 35.8),                                      # U3 interior
                  ('B.Cu', 57.9, 25.8, 63.72, 28.1), ('B.Cu', 61.7, 28.1, 63.72, 35.8),  # U3 interior on B.Cu round the pocket of C2
                  ('B.Cu', 57.9, 33.6, 61.7, 35.8),                                      # (bottom, at U3.2 / U3.3: placement.py)
                  ('B.Cu', 53.5, 26.2, 56.1, 35.8),                                       # strip between U2 and U3 (B.Cu)
                  ('B.Cu', 43.5, 35.9, 56.1, 38.5)]   # 2.10: below the U2 pin rows (SRV_I_L_OUT / SRV_ADC_AIN / REF25 cut C1 -> U2.4, 36 mm)
ROUTER_KEEPOUT += ANALOG_KEEPOUT
PLANNER_KEEPOUT = list(ROUTER_KEEPOUT)   # the completion planner (complete_routes.py) keeps out too
TOP_ONLY = []                # nets in a DSN class limited to F.Cu (use_layer; prepare_routing.py, complete_routes.py). Tried 2.10 for SW_SENSE
                             # (review F3: 163 mm, most on B.Cu below the analog block): on F.Cu alone the router and the planner could not reach
                             # U6.5 between R15 / R16 (no complete board); SW_SENSE stays on both layers (static, 1k / 100k)
# review 2.10 (F2): GND vias placed by stitch.py after the completion planner, nearest legal spot to each target (both pours, own pad's
# pour piece): ('pad', ref, num, radius) - at a capacitor GND pad; ('at', x, y, radius) - a free spot (the B.Cu island under U2 / U3 had
# one via). Every SMD decoupling / filter capacitor gets one (verify_pcb.py measures the return to its part's GND pin).
EXTRA_GND_VIAS = [('pad', c, '2', 2.0) for c in ('C1', 'C2', 'C4', 'C5', 'C6', 'C7', 'C8', 'C9', 'C10', 'C11', 'C12', 'C13', 'C14', 'C15', 'C16')] + \
                 [('pad', 'U1', '2', 2.0), ('at', 54.8, 31.4, 2.0), ('at', 60.8, 33.5, 2.0)]   # U1.2: INA240 GND (C6 return)
SHUNT = 'RSH1'               # check_intrusion.py: no router copper of another net in its courtyard (README: nothing under the shunt)
# 2.10 (verify_pcb.py return-path check): capacitor -> GND pin of its part; complete_routes.py --ties plans a GND track where the
# GND copper path is longer than 1.3 x straight + 3 mm
RETURN_PAIRS = {'C1': ('U2', '4'), 'C2': ('U3', '3'), 'C4': ('U4', '1'), 'C5': ('U10', '1'), 'C6': ('U1', '2'), 'C7': ('U2', '4'), 'C8': ('U3', '4'),
                'C9': ('U4', '1'), 'C10': ('U5', '7'), 'C11': ('U6', '7'), 'C12': ('U7', '7'), 'C13': ('U8', '3'), 'C14': ('U9', '3'),
                'C15': ('U10', '1'), 'C16': ('U3', '4')}
